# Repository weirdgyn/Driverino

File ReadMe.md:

# Driverino 

### (italian noun) /ˈdraɪvərnəʊ/ : *little driver*

Driverino is a pretty simple, low power, driver for [BLDC](https://en.wikipedia.org/wiki/Brushless_DC_electric_motor) sensored motors.
The project target was to create a very small unit capable of driving a motor rated about 50-100W.
The board is fitted with ATmega32U4 micro the same of Arduino Micro Pro commercial boards, once the correct bootloader has been burned-in the board should act as an Arduino board (at least for programming/debugging task) and also spin a motor.
The project includes:
 1. Fully designed 2 layers PCB board (KiCAD);
 2. Driverino firmware sources;
 3. MCT8316Z library sources.

Driverino's firmware allow users to drive BLDC motors using a standard [RS232](https://en.wikipedia.org/wiki/RS-232) interface trough simple interactive commands.
The firmware allows also:
* closed loop speed control (implementing a [PID](https://en.wikipedia.org/wiki/PID_controller) loop);
* motor/driver status monitoring;
* R/C ESC emulation.

The library allows Arduino users to interact with BLDC motors without knowledge of MCT8316Z chip and [SPI](https://en.wikipedia.org/wiki/Serial_Peripheral_Interface) protocol.

## Driverino features

* ATmega32U4 microcontroller;
* Micro [USB](https://en.wikipedia.org/wiki/USB) interface;
* MCT8316Z motor driver;
* 41x26mm (size);
* RS232 interface;
* Standard R/C input compatibile.

The board can drive up to 24V-36V 8A rated sensored BLDC motors and provide 5V power supply (200mA max) mimicking R/C ESC BEC feature.
Driverino supports a variety of different types of [Hall](https://en.wikipedia.org/wiki/Hall_effect_sensor)'s sensors (analog single ended, analog differtial, digital) and also different sensors supply rates (3.3V and 5V). To correctly fit for a specific sensor kind some soldering may be required: by default the board project is fitted for digital 5V sensors.

## Firmware

TBD

## Library

TBD

# TODO:

- [ ] Add features:
   - [ ] vm measurement;
   - [ ] current measurement (via INA250).
- [ ] Optimize PCB layout.
- [ ] Write Library.
- [ ] Write Firmware.
- [ ] Submit to Kitspace
- [ ] Submit to Made-With-KiCAD

# Links

* [Atmel/Microchip ATMega32U4](https://www.microchip.com/wwwproducts/en/ATmega32U4)
* [TI MCT8316Z](https://www.ti.com/product/MCT8316Z?keyMatch=MCT8316Z&tisearch=search-everything)
* [Arduino](https://www.arduino.cc/)
* [KiCAD](https://www.kicad.org/)

#

Live long and prosper!

That's all folks.

By[t]e{s} Weirdgyn

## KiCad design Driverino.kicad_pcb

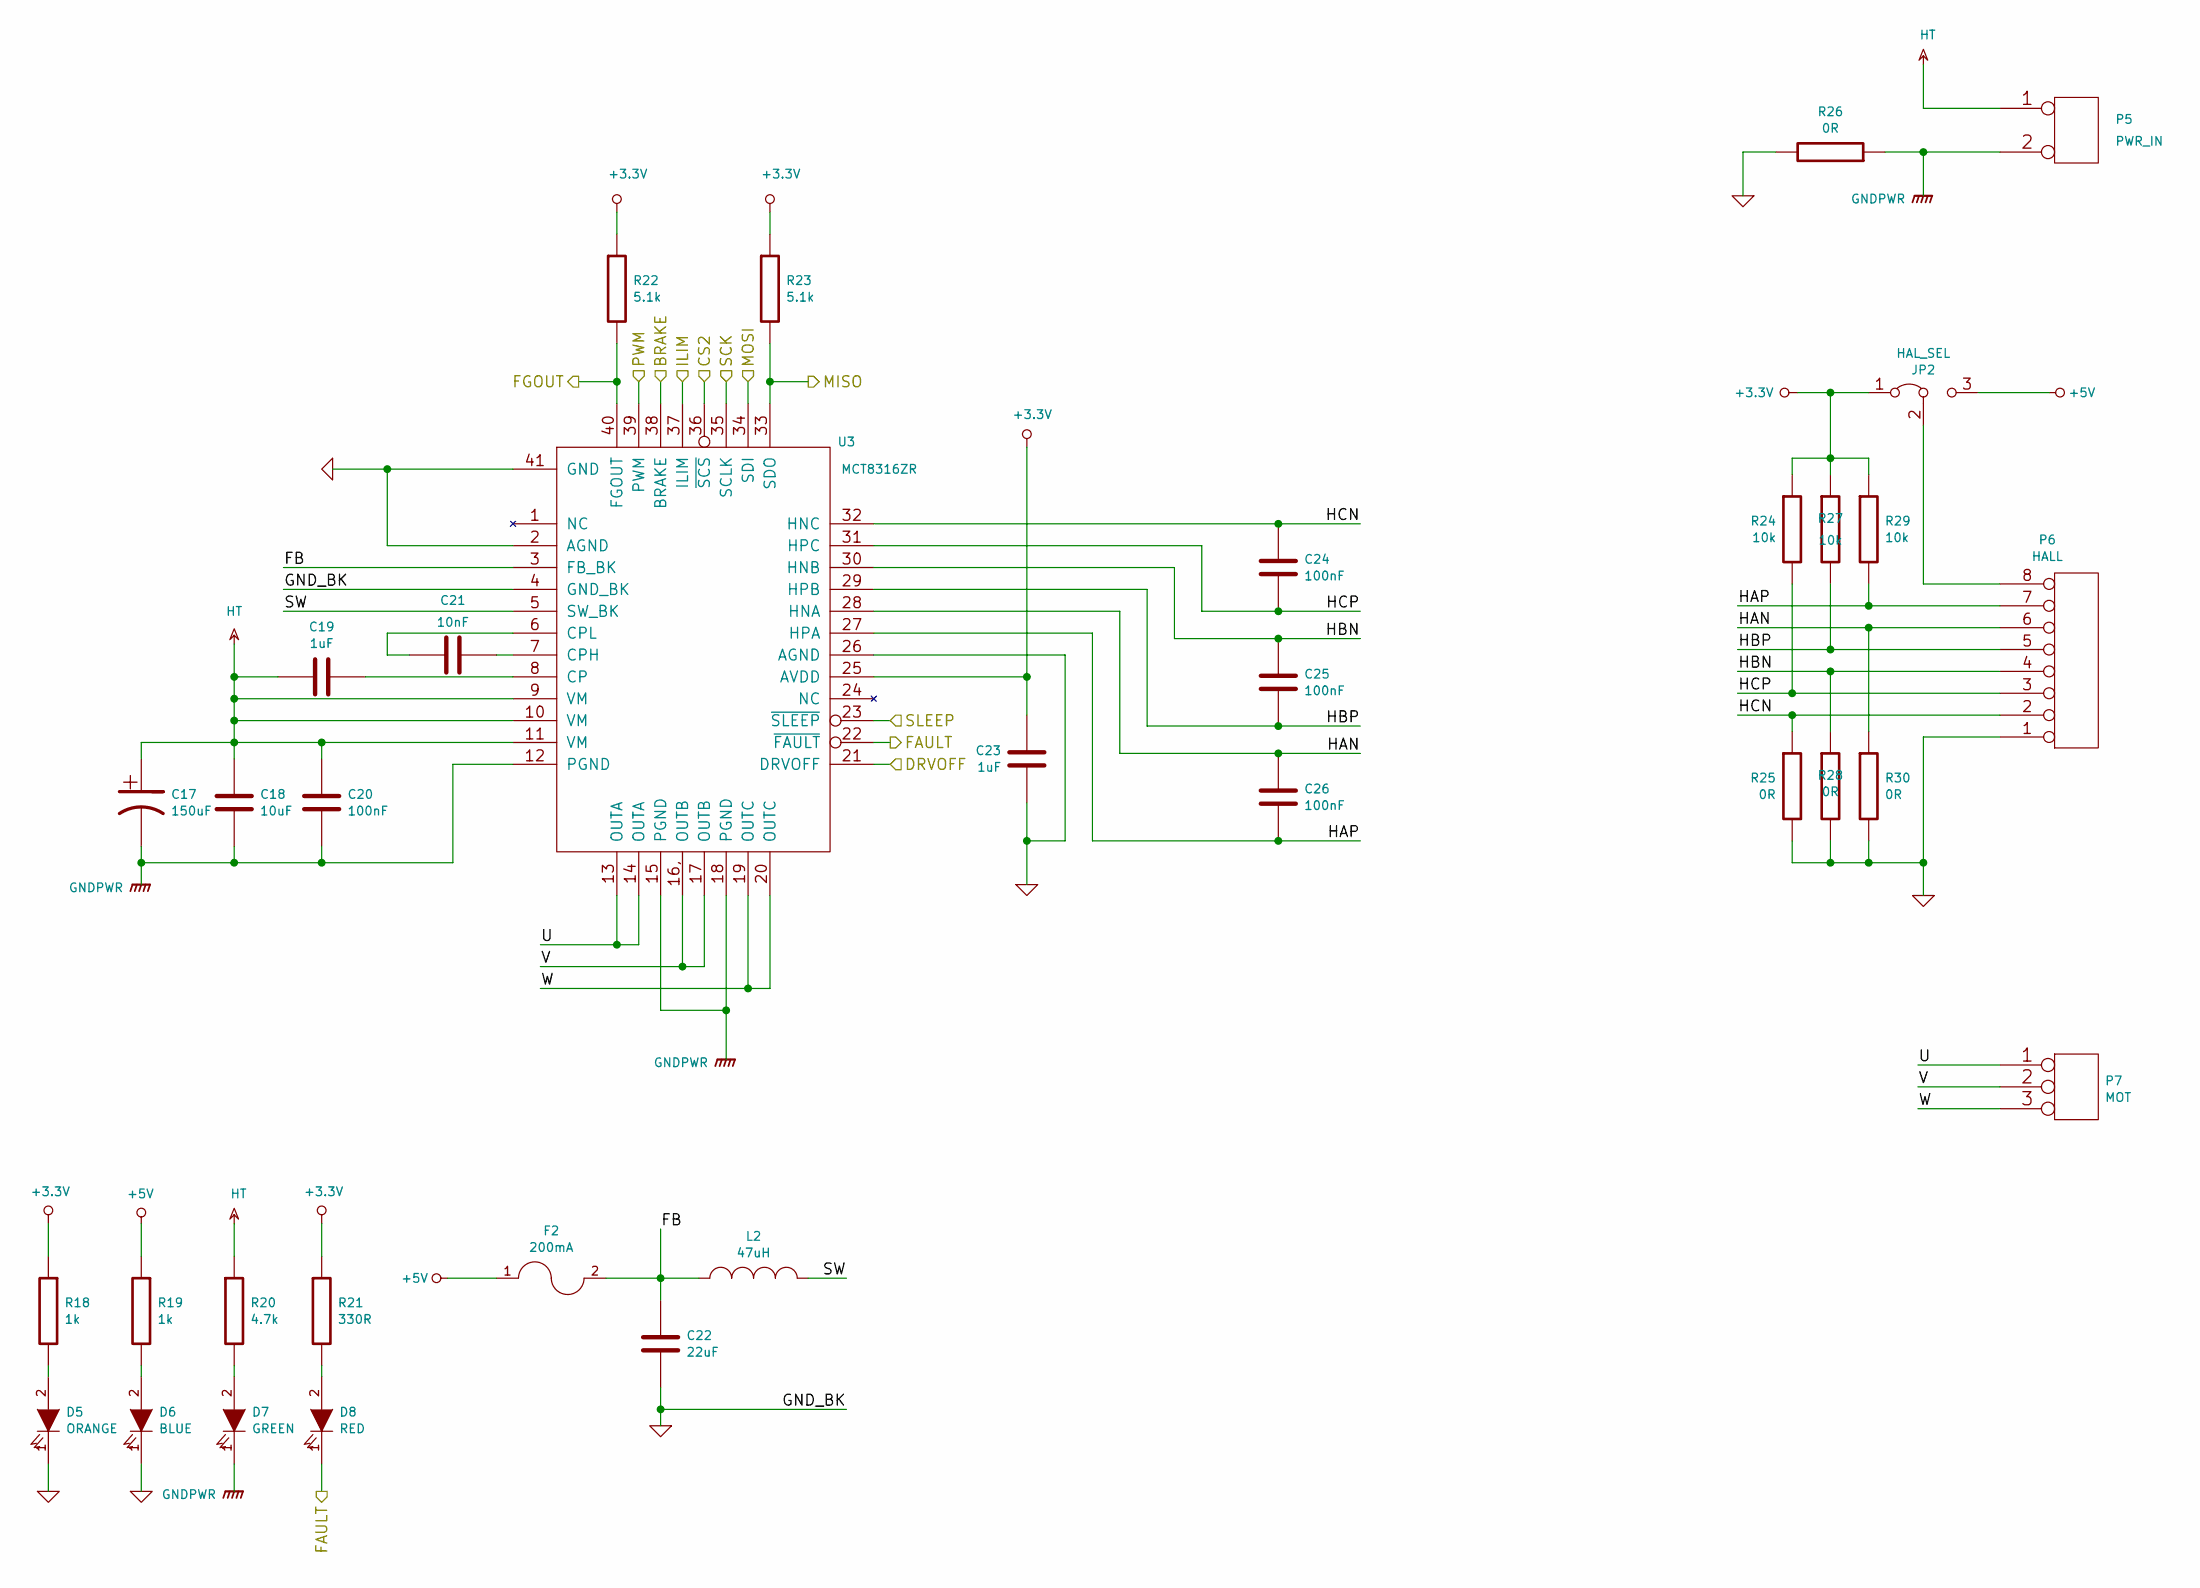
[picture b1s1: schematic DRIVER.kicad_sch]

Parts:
C17: 150uF; CP_Elec_6.3x7.7
C18: 10uF; C_1206_3216Metric
C19, C23: 1uF; C_0603_1608Metric
C20, C24, C25, C26: 100nF; C_0402_1005Metric
C21: 10nF; C_0402_1005Metric
C22: 22uF; C_1206_3216Metric
D5: ORANGE; LED_0603_1608Metric
D6: BLUE; LED_0603_1608Metric
D7: GREEN; LED_0603_1608Metric
D8: RED; LED_0603_1608Metric
F2: 200mA; Fuse_0402_1005Metric
JP2: HAL_SEL; PinHeader_1x03_P1.27mm_Vertical
L2: 47uH; L_1210_3225Metric
P5: PWR_IN; 39773-0002
P6: HALL; Molex_PicoBlade_53047-0810_1x08_P1.25mm_Vertical
P7: MOT; 39773-0003
R18, R19: 1k; R_0402_1005Metric
R20: 4.7k; R_0402_1005Metric
R21: 330R; R_0402_1005Metric
R22, R23: 5.1k; R_0402_1005Metric
R24, R27, R29: 10k; R_0402_1005Metric
R25, R26, R28, R30: 0R; R_0402_1005Metric
U3: MCT8316ZR; QFN-40_EP_5x7_Pitch0.5mm

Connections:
+3.3V: C23.2, JP2.1 (A), R18.1, R21.1, R22.1, R23.1, R24.1, R27.1, R29.1, U3.25 (AVDD)
+5V: F2.1, JP2.3 (B), R19.1; also elsewhere on the board
/ARDUINO-MICRO/BRAKE: U3.38 (BRAKE); also elsewhere on the board
/ARDUINO-MICRO/CS2: U3.36 (~SCS); also elsewhere on the board
/ARDUINO-MICRO/DRVOFF: U3.21 (DRVOFF); also elsewhere on the board
/ARDUINO-MICRO/FAULT: D8.1 (K), U3.22 (~FAULT); also elsewhere on the board
/ARDUINO-MICRO/FGOUT: R22.2, U3.40 (FGOUT); also elsewhere on the board
/ARDUINO-MICRO/ILIM: U3.37 (ILIM); also elsewhere on the board
/ARDUINO-MICRO/MISO: R23.2, U3.33 (SDO); also elsewhere on the board
/ARDUINO-MICRO/MOSI: U3.34 (SDI); also elsewhere on the board
/ARDUINO-MICRO/PWM: U3.39 (PWM); also elsewhere on the board
/ARDUINO-MICRO/SCK: U3.35 (SCLK); also elsewhere on the board
/DRIVER/FB: C22.2, F2.2, L2.2, U3.3 (FB_BK)
/DRIVER/HAN: C26.2, P6.6, R30.1, U3.28 (HNA)
/DRIVER/HAP: C26.1, P6.7, R29.2, U3.27 (HPA)
/DRIVER/HBN: C25.2, P6.4, R28.1, U3.30 (HNB)
/DRIVER/HBP: C25.1, P6.5, R27.2, U3.29 (HPB)
/DRIVER/HCN: C24.2, P6.2, R25.1, U3.32 (HNC)
/DRIVER/HCP: C24.1, P6.3, R24.2, U3.31 (HPC)
/DRIVER/SLEEP: U3.23 (~SLEEP)
/DRIVER/SW: L2.1, U3.5 (SW_BK)
/DRIVER/U: P7.1, U3.13 (OUTA), U3.14 (OUTA)
/DRIVER/V: P7.2 (PM), U3.16, U3.16, (OUTB), U3.17 (OUTB)
/DRIVER/W: P7.3, U3.19 (OUTC), U3.20 (OUTC)
GND: C22.1, C23.1, D5.1 (K), D6.1 (K), P6.1, R25.2, R26.2, R28.2, R30.2, U3.2 (AGND), U3.4 (GND_BK), U3.26 (AGND), U3.41 (GND); also elsewhere on the board
GNDPWR: C17.2, C18.2, C20.2, D7.1 (K), P5.2 (PM), R26.1, U3.12 (PGND), U3.15 (PGND), U3.18 (PGND)
HT: C17.1, C18.1, C19.2, C20.1, P5.1, R20.1, U3.9 (VM), U3.10 (VM), U3.11 (VM)
unnamed: C19.1, U3.8 (CP)
unnamed: C21.1, U3.7 (CPH)
unnamed: C21.2, U3.6 (CPL)
unnamed: D5.2 (A), R18.2
unnamed: D6.2 (A), R19.2
unnamed: D7.2 (A), R20.2
unnamed: D8.2 (A), R21.2
unnamed: JP2.2 (C), P6.8

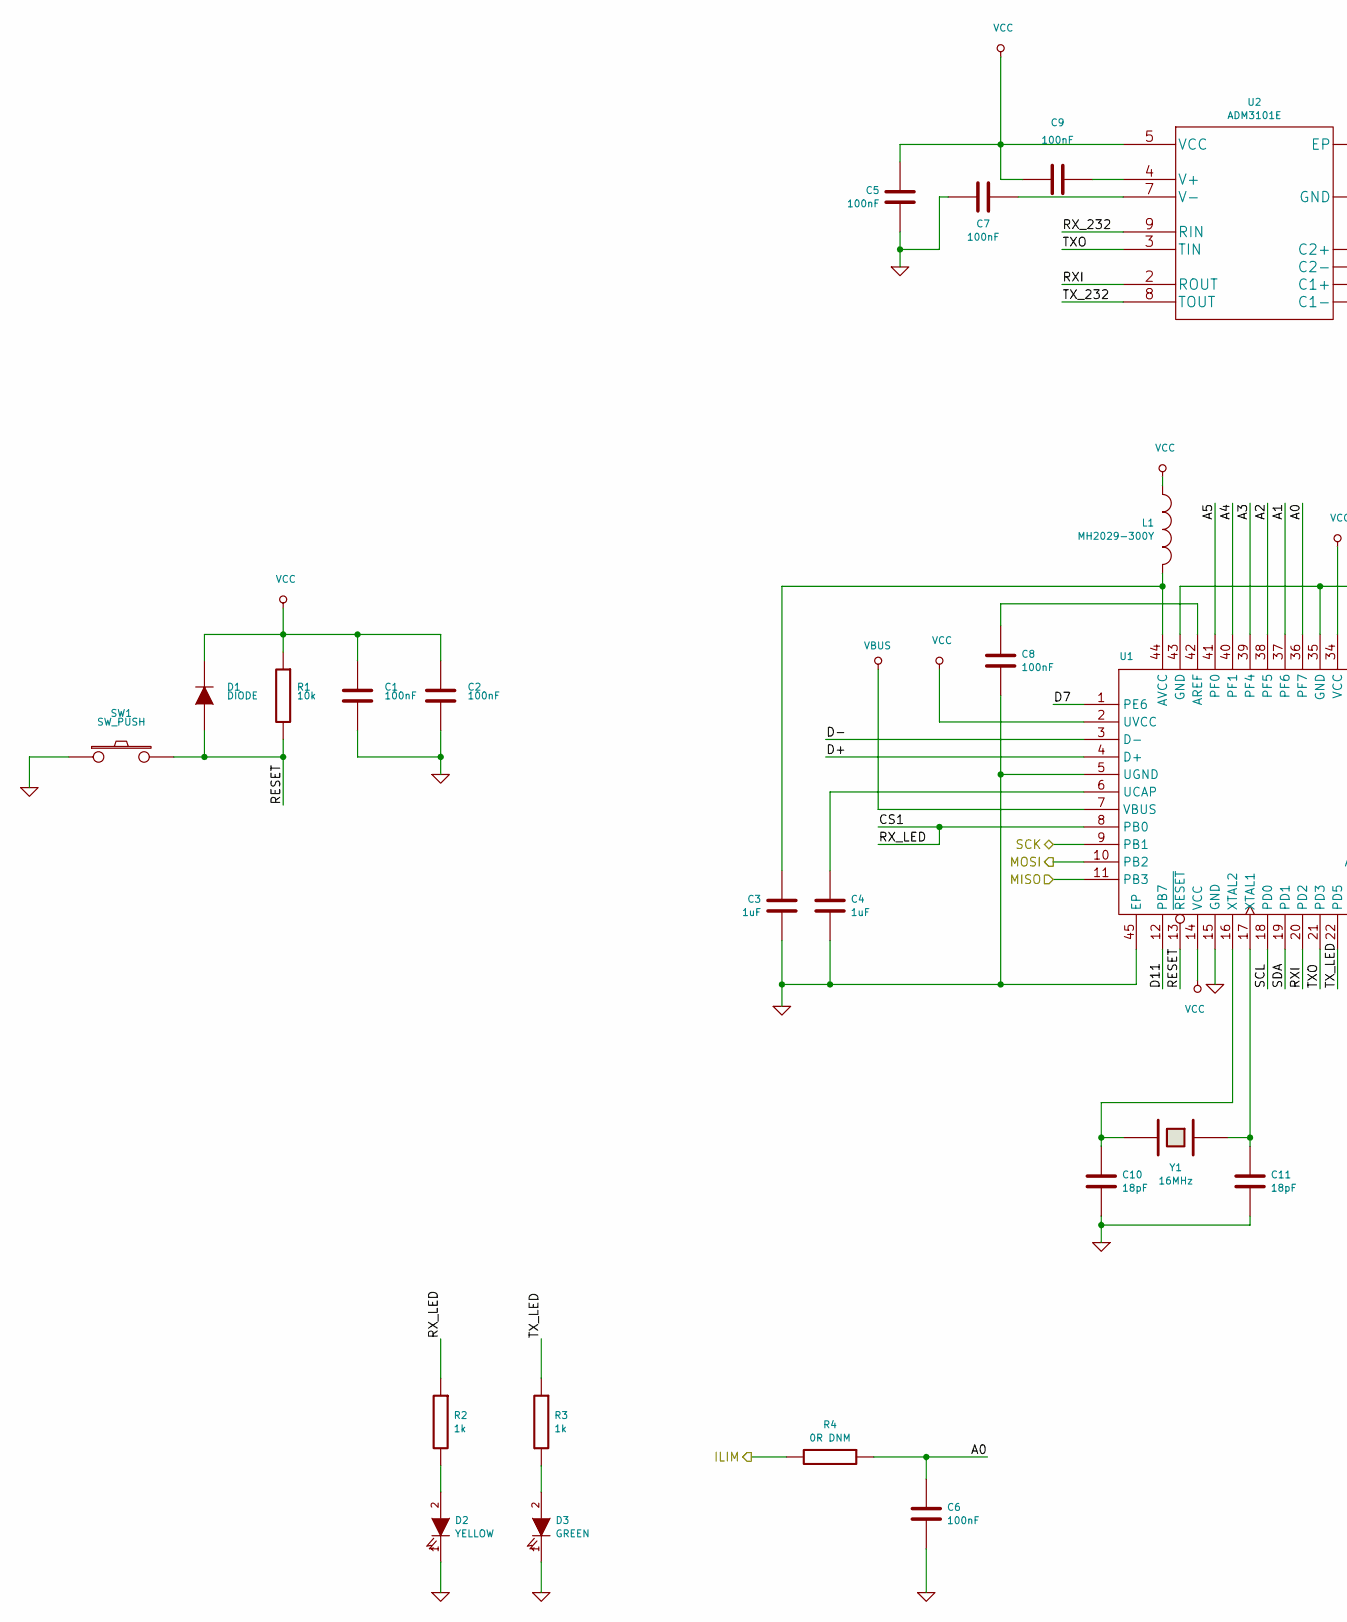
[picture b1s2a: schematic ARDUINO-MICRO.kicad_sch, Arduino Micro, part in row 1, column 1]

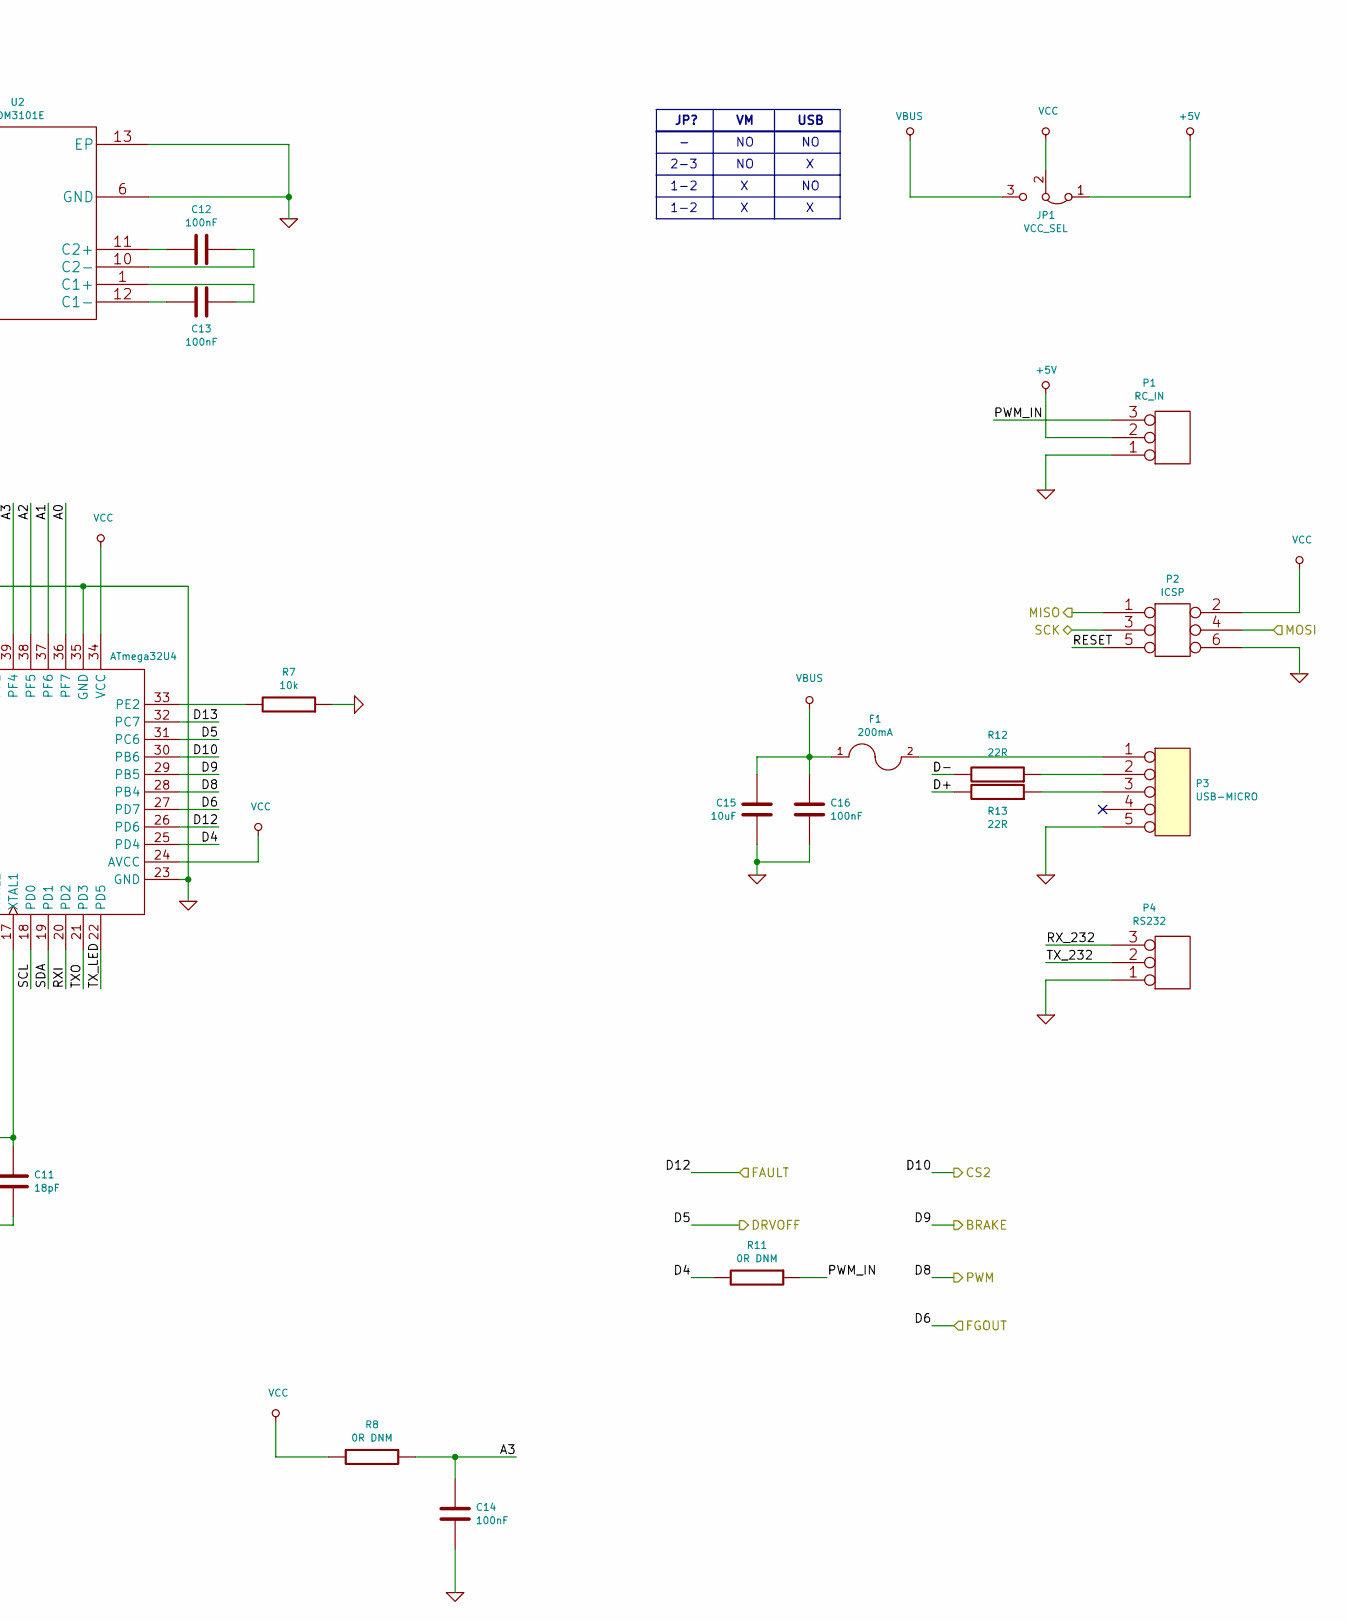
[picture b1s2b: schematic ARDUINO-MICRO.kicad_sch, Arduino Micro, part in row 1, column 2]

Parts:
C1, C2, C5, C6, C7, C8, C9, C12, C13, C14, C16: 100nF; C_0402_1005Metric
C3, C4: 1uF; C_0603_1608Metric
C10, C11: 18pF; C_0402_1005Metric
C15: 10uF; C_1206_3216Metric
D1: DIODE; D_0402_1005Metric
D2: YELLOW; LED_0603_1608Metric
D3: GREEN; LED_0603_1608Metric
F1: 200mA; Fuse_0402_1005Metric
JP1: VCC_SEL; PinHeader_1x03_P1.27mm_Vertical
L1: MH2029-300Y; R_0805_2012Metric
P1: RC_IN; PinHeader_1x03_P2.54mm_Horizontal
P2: ICSP; PinHeader_2x03_P2.54mm_Vertical
P3: USB-MICRO; USB_Micro-B_Amphenol_10103594-0001LF_Horizontal
P4: RS232; Molex_PicoBlade_53047-0310_1x03_P1.25mm_Vertical
R1, R7: 10k; R_0402_1005Metric
R2, R3: 1k; R_0402_1005Metric
R4, R8, R11: 0R DNM; R_0402_1005Metric
R12, R13: 22R; R_0402_1005Metric
SW1: SW_PUSH; SW_SPST_B3U-1000P
U1: ATmega32U4; QFN-44-1EP_7x7mm_P0.5mm_EP5.2x5.2mm
U2: ADM3101E; CP-12-4
Y1: 16MHz; Crystal_SMD_2016-4Pin_2.0x1.6mm

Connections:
+5V: JP1.1 (A), P1.2 (PM); also elsewhere on the board
/ARDUINO-MICRO/A0: C6.2, R4.1, U1.36 (PF7)
/ARDUINO-MICRO/A1: U1.37 (PF6)
/ARDUINO-MICRO/A2: U1.38 (PF5)
/ARDUINO-MICRO/A3: C14.2, R8.1, U1.39 (PF4)
/ARDUINO-MICRO/A4: U1.40 (PF1)
/ARDUINO-MICRO/A5: U1.41 (PF0)
/ARDUINO-MICRO/BRAKE: U1.29 (PB5); also elsewhere on the board
/ARDUINO-MICRO/CS1: R2.1, U1.8 (PB0)
/ARDUINO-MICRO/CS2: U1.30 (PB6); also elsewhere on the board
/ARDUINO-MICRO/D4: R11.2, U1.25 (PD4)
/ARDUINO-MICRO/D7: U1.1 (PE6)
/ARDUINO-MICRO/D11: U1.12 (PB7)
/ARDUINO-MICRO/D13: U1.32 (PC7)
/ARDUINO-MICRO/D+: R13.2, U1.4 (D+)
/ARDUINO-MICRO/D-: R12.2, U1.3 (D-)
/ARDUINO-MICRO/DRVOFF: U1.31 (PC6); also elsewhere on the board
/ARDUINO-MICRO/FAULT: U1.26 (PD6); also elsewhere on the board
/ARDUINO-MICRO/FGOUT: U1.27 (PD7); also elsewhere on the board
/ARDUINO-MICRO/ILIM: R4.2; also elsewhere on the board
/ARDUINO-MICRO/MISO: P2.1, U1.11 (PB3); also elsewhere on the board
/ARDUINO-MICRO/MOSI: P2.4, U1.10 (PB2); also elsewhere on the board
/ARDUINO-MICRO/PWM: U1.28 (PB4); also elsewhere on the board
/ARDUINO-MICRO/PWM_IN: P1.3, R11.1
/ARDUINO-MICRO/RESET: D1.2 (A), P2.5, R1.2, SW1.2, U1.13 (~RESET)
/ARDUINO-MICRO/RXI: U1.20 (PD2), U2.2 (ROUT)
/ARDUINO-MICRO/RX_232: P4.3, U2.9 (RIN)
/ARDUINO-MICRO/SCK: P2.3, U1.9 (PB1); also elsewhere on the board
/ARDUINO-MICRO/SCL: U1.18 (PD0)
/ARDUINO-MICRO/SDA: U1.19 (PD1)
/ARDUINO-MICRO/TXO: U1.21 (PD3), U2.3 (TIN)
/ARDUINO-MICRO/TX_232: P4.2 (PM), U2.8 (TOUT)
/ARDUINO-MICRO/TX_LED: R3.1, U1.22 (PD5)
GND: C1.1, C2.1, C3.1, C4.1, C5.2, C6.1, C7.2, C8.1, C10.2, C11.2, C14.1, C15.1, C16.1, D2.1 (K), D3.1 (K), P1.1, P2.6, P3.5, P4.1, R7.1, SW1.1, U1.5 (UGND), U1.15 (GND), U1.23 (GND), U1.35 (GND), U1.43 (GND), U1.45 (EP), U2.6 (GND), U2.13 (EP); also elsewhere on the board
unnamed: C3.2, L1.2, U1.44 (AVCC)
unnamed: C4.2, U1.6 (UCAP)
unnamed: C7.1, U2.7 (V-)
unnamed: C8.2, U1.42 (AREF)
unnamed: C9.2, U2.4 (V+)
unnamed: C10.1, U1.16 (XTAL2), Y1.2
unnamed: C11.1, U1.17 (XTAL1), Y1.1
unnamed: C12.1, U2.10 (C2-)
unnamed: C12.2, U2.11 (C2+)
unnamed: C13.1, U2.1 (C1+)
unnamed: C13.2, U2.12 (C1-)
unnamed: D2.2 (A), R2.2
unnamed: D3.2 (A), R3.2
unnamed: F1.2, P3.1
unnamed: P3.2, R12.1
unnamed: P3.3, R13.1
unnamed: R7.2, U1.33 (PE2)
VBUS: C15.2, C16.2, F1.1, JP1.3 (B), U1.7 (VBUS)
VCC: C1.2, C2.2, C5.1, C9.1, D1.1 (K), JP1.2 (C), L1.1, P2.2, R1.1, R8.2, U1.2 (UVCC), U1.14 (VCC), U1.24 (AVCC), U1.34 (VCC), U2.5 (VCC)

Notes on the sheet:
1-2
JP?
2-3
USB

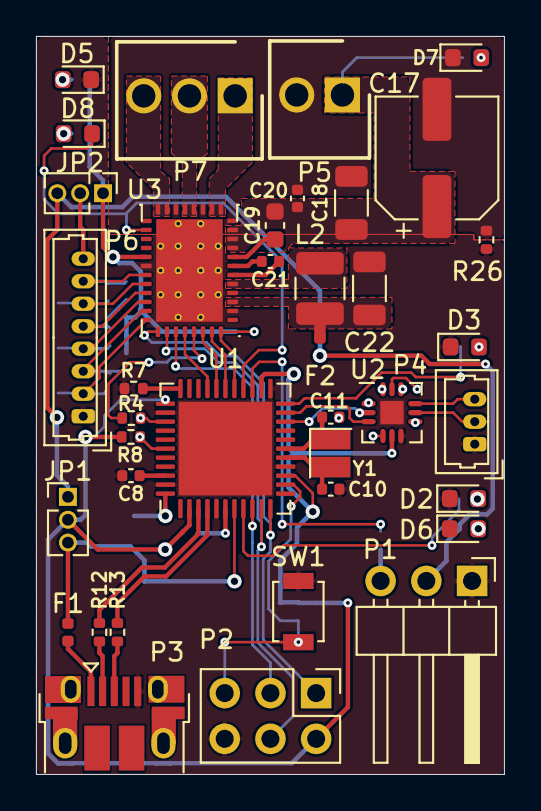
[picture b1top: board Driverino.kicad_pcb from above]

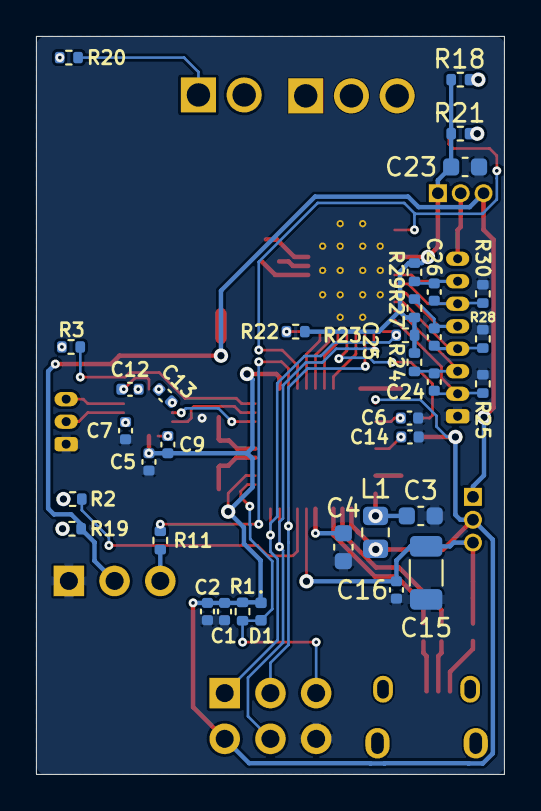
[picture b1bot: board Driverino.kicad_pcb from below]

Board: 2 copper layers, 26.0 x 41.0 mm, 73 parts (35 on the bottom side), 66 nets.

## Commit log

2021-04-29 Defined schematics hierarchy
2021-05-05 Routing completed
2021-05-05 Gerber plot
2021-05-05 Modified F1
2021-05-12 Create LICENSE
2024-05-21 Update LICENSE
2024-05-21 Update to KiCAD 8.0
    Update to KiCAD 8.0

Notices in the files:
parts and their libraries:
Copyright 2016 Accelerated Designs. All rights reserved.
